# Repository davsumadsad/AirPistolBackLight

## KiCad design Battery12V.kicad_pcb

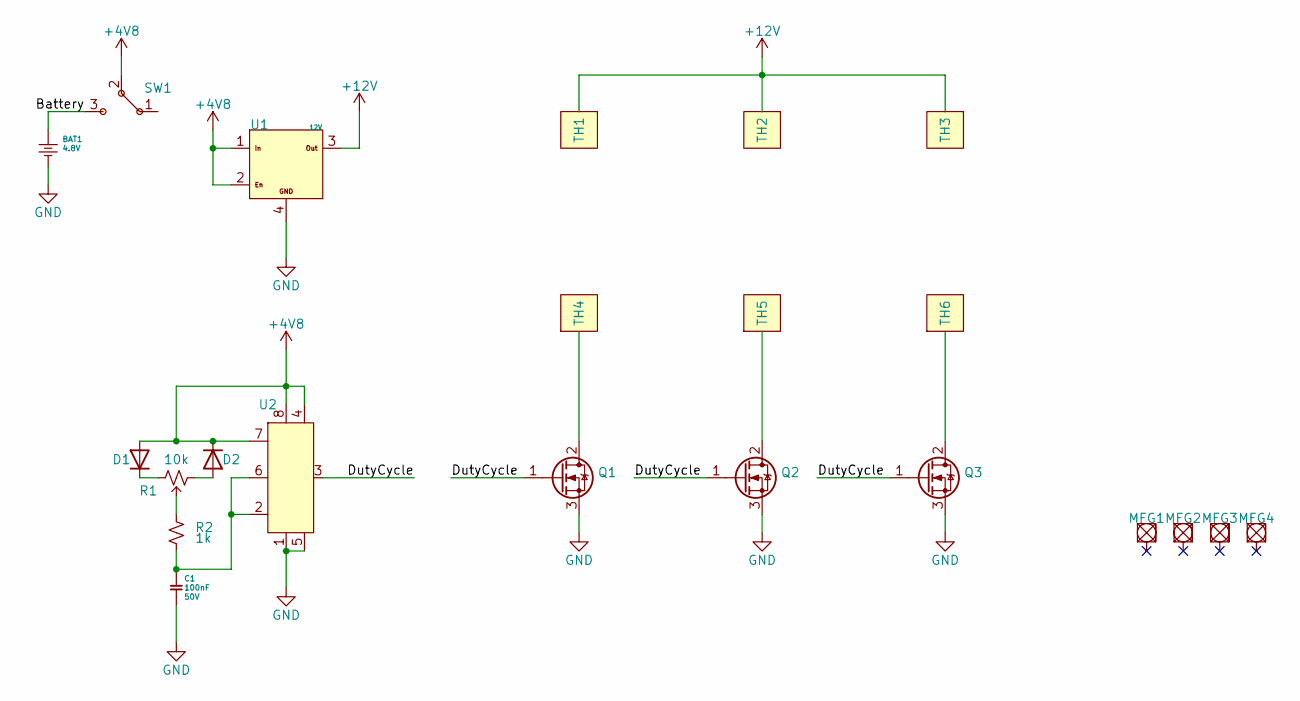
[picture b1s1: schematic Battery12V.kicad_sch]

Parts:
BAT1: 2481; BAT_2481; Voltage 4.8V; MFG_PN 2481
C1: 100nF; C_Rect_L7.0mm_W3.5mm_P5.00mm; Voltage 50V; MFG_PN C1608X7R1H104K080AA
D1, D2: 1N914; D_DO-35_SOD27_P7.62mm_Horizontal
MFG1, MFG2, MFG3, MFG4: M.3
Q1, Q2, Q3: IRLML2803PBF; SOT-23
R1: 10k; PTN16_SAME_SKY; MFG_PN PDB12-H4301-103BF
R2: 1k; R_Axial_DIN0204_L3.6mm_D1.6mm_P5.08mm_Horizontal; MFG_PN RC0603FR-071KL
SW1: ROCKER_SWITCH
TH1, TH2, TH3, TH4, TH5, TH6: Pad_9x2_mm
U1: 12V; Adafruit-TPS61040-PCB-main; MFG_PN TPS61040
U2: DIP-8_W7.62mm

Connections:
+4V8: D1.2 (A), D2.1 (K), SW1.2, U1.1, U1.2, U2.4, U2.7, U2.8
+12V: TH1.1, TH2.1, TH3.1, U1.3
/Battery: BAT1.1, SW1.3
/DutyCycle: Q1.1 (G), Q2.1 (G), Q3.1 (G), U2.3
GND: BAT1.2, C1.2, Q1.3 (S), Q2.3 (S), Q3.3 (S), U1.4, U2.1, U2.5
unnamed: C1.1, R2.2, U2.2, U2.6
unnamed: D1.1 (K), R1.3
unnamed: D2.2 (A), R1.1
unnamed: Q1.2 (D), TH4.1
unnamed: Q2.2 (D), TH5.1
unnamed: Q3.2 (D), TH6.1
unnamed: R1.2, R2.1

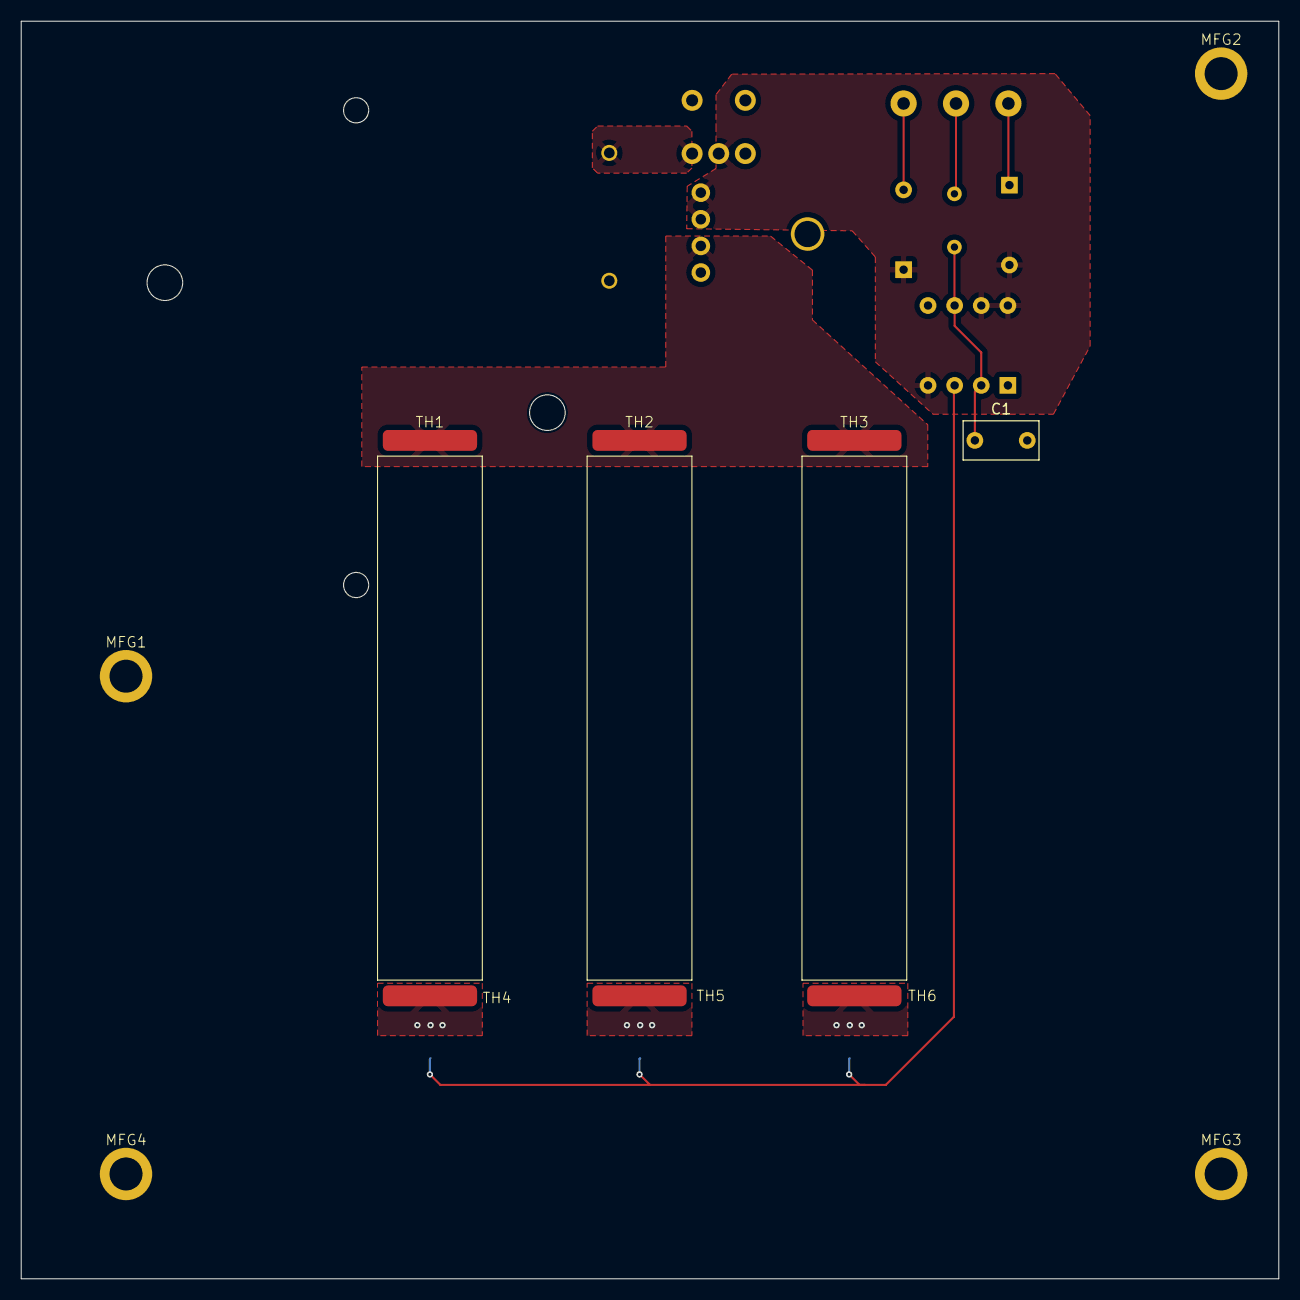
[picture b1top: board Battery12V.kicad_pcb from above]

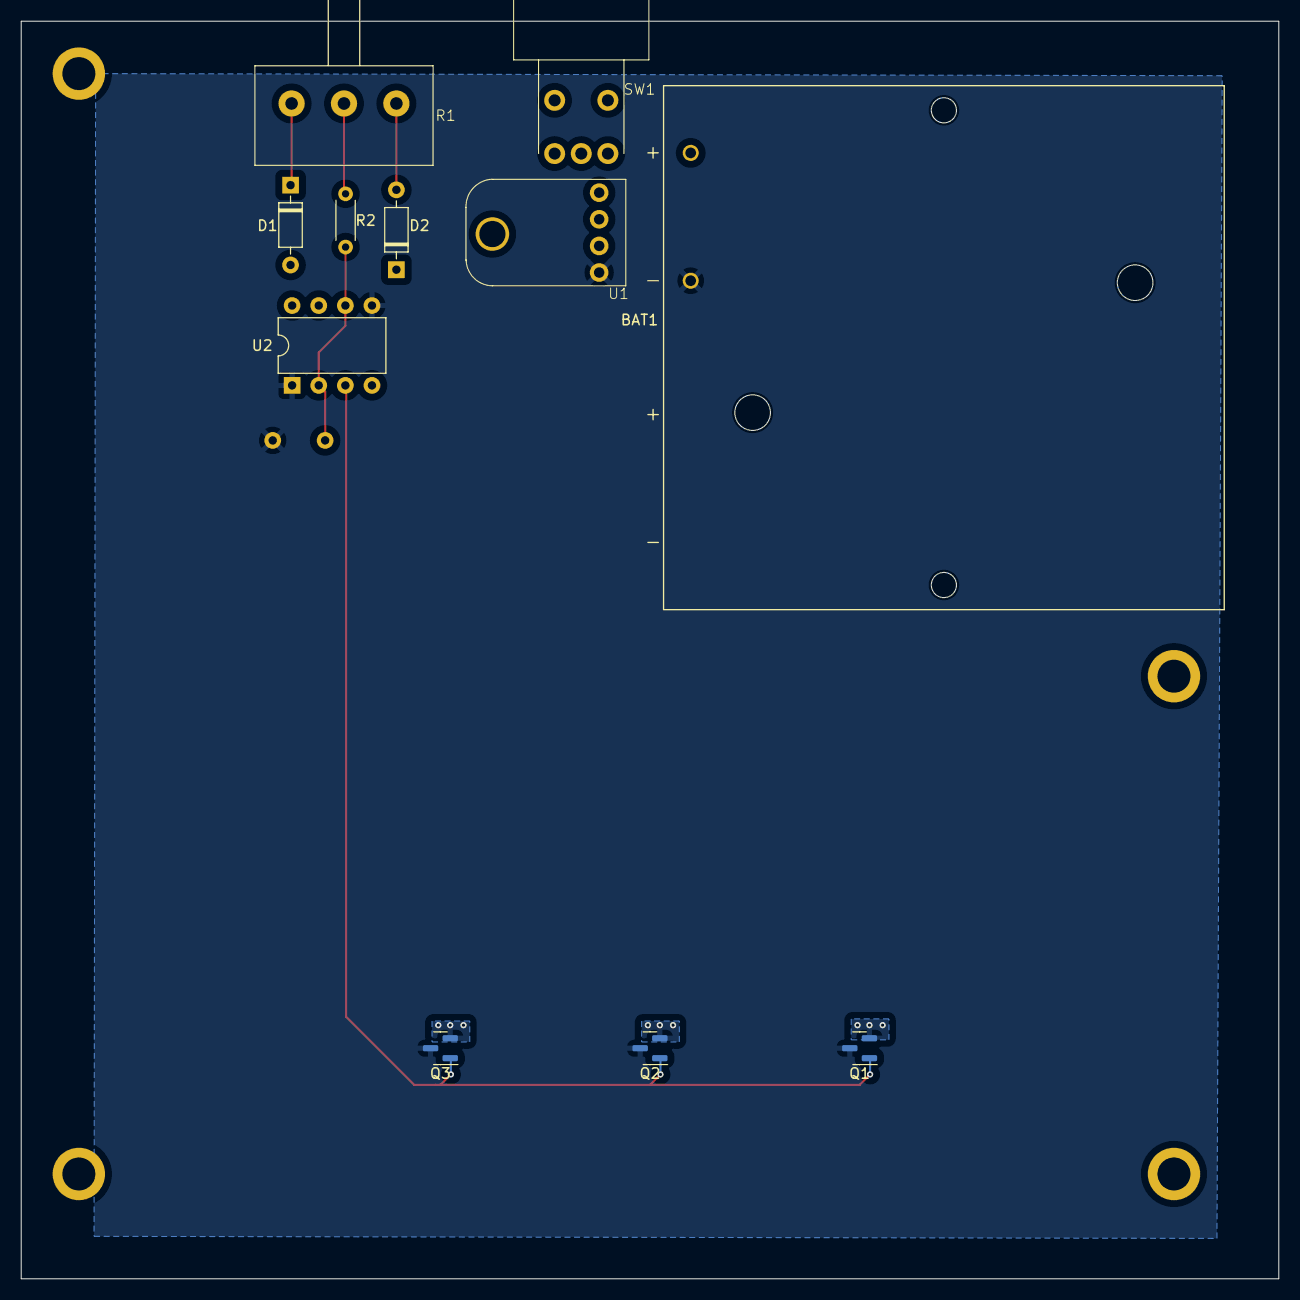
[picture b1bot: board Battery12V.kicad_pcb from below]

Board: 2 copper layers, 120.0 x 120.0 mm, 22 parts (11 on the bottom side), 12 nets.
